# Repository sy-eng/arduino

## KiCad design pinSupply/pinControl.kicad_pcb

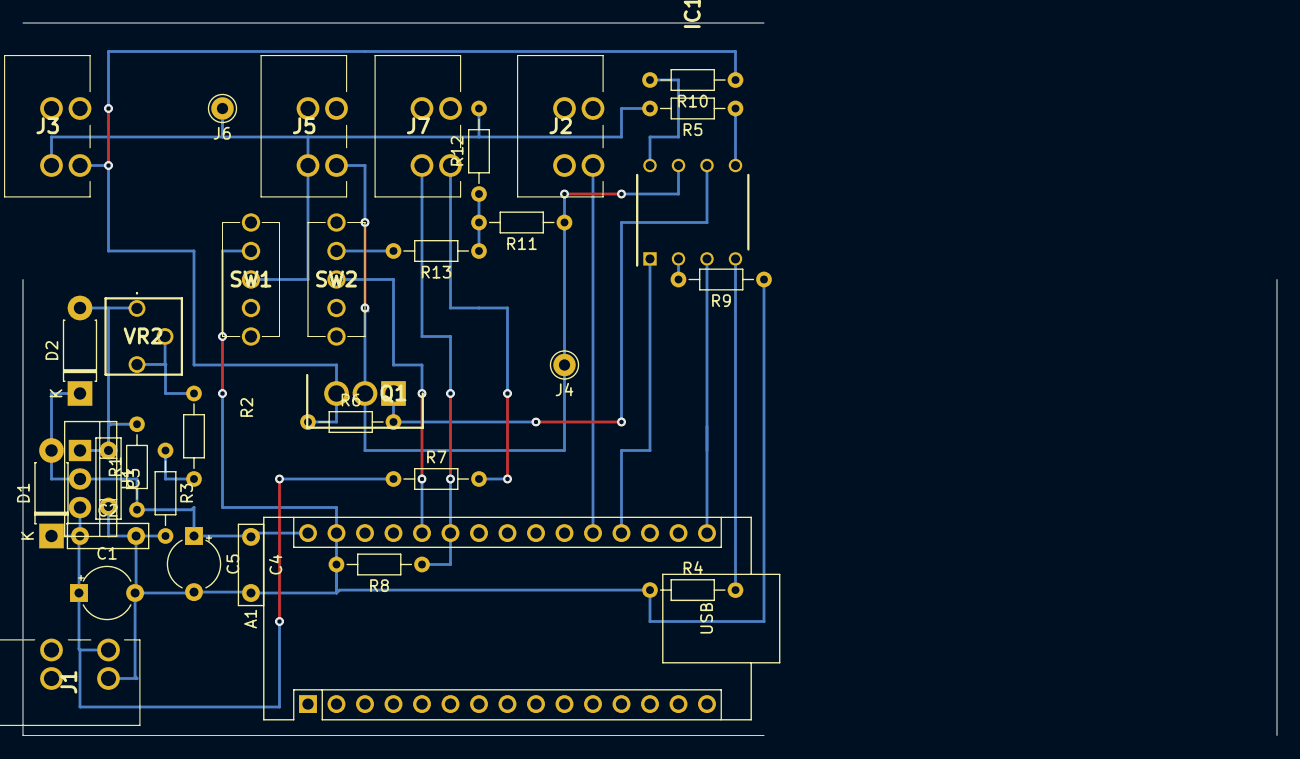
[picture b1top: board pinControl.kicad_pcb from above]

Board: 2 copper layers, 111.8 x 63.5 mm, 34 parts (0 on the bottom side), 22 nets.

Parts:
A1: Arduino_Nano_v3.x; Arduino_Nano
C1, C5: 47u; CP_Radial_Tantal_D4.5mm_P5.00mm
C2, C3: 0.1u; C_Rect_L7.0mm_W2.0mm_P5.00mm
C4: 1u; C_Rect_L7.0mm_W2.0mm_P5.00mm
D1, D2: D; D_DO-41_SOD81_P7.62mm_Horizontal
IC1: TLP521-2; DIP832W60P254L966H380Q8N
J1, J2, J3, J5, J7: TB401-1-2-E; TB40112E
J4, J6: Conn_01x01_Male; Pin_D1.0mm_L10.0mm
Q1: 2SJ334; TO254P470X1000X2090-3P
R1: 220; R_Axial_DIN0204_L3.6mm_D1.6mm_P7.62mm_Horizontal
R2: 100; R_Axial_DIN0204_L3.6mm_D1.6mm_P7.62mm_Horizontal
R3, R13: 1k; R_Axial_DIN0204_L3.6mm_D1.6mm_P7.62mm_Horizontal
R4, R8, R9: 470; R_Axial_DIN0204_L3.6mm_D1.6mm_P7.62mm_Horizontal
R5, R6: 4.7k; R_Axial_DIN0204_L3.6mm_D1.6mm_P7.62mm_Horizontal
R7, R10, R12: 2.2k; R_Axial_DIN0204_L3.6mm_D1.6mm_P7.62mm_Horizontal
R11: 10k; R_Axial_DIN0204_L3.6mm_D1.6mm_P7.62mm_Horizontal
SW1, SW2: 2MS1T1B4VS2QES
U1: LM317_TO-220; TO-220-3_Vertical
VR2: GF063P 200; GF063P

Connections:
+8V: A1.30 (VIN), C4.1, C5.1, D1.2 (A), D2.1 (K), R1.1, U1.2 (VO)
+24V: C1.1, C2.1, D1.1 (K), J1.3, R7.1, U1.3 (VI)
GND: A1.29 (GND), C1.2, C2.2, C3.2, C4.2, C5.2, J1.4, R3.2, R4.1, R8.2, R9.1, SW1.1 (NO)
GNDPWR: J3.4, J5.4, J6.1, R5.2, R12.2, SW1.2 (COM)
unnamed: A1.16 (D13), IC1.3 (ANODE_2)
unnamed: A1.19 (A0), IC1.1 (ANODE_1)
unnamed: A1.20 (A1), J2.3
unnamed: C3.1, D2.2 (A), R1.2, U1.1 (ADJ), VR2.1 (CCW)
unnamed: IC1.2 (CATHODE_1), R9.2
unnamed: IC1.4 (CATHODE_2), R4.2
unnamed: IC1.5 (EMITTER_1), R5.1
unnamed: IC1.6 (COLLECTOR_1), Q1.1, R6.2
unnamed: IC1.7 (EMITTER_2), J4.1, J5.3, Q1.2, R11.1
unnamed: IC1.8 (COLLECTOR_2), R10.2
unnamed: J7.3, R7.2
unnamed: R2.1, VR2.2 (WIPER), VR2.3 (CW)
unnamed: R2.2, R3.1
unnamed: R11.2, R12.1, R13.1
unnamed: R13.2, SW2.1 (NO)
OUT_REF: A1.26 (A7), SW2.2 (COM)
PROX_OUT: A1.25 (A6), J7.4, R8.1
VPP: J3.3, Q1.3, R6.1, R10.1

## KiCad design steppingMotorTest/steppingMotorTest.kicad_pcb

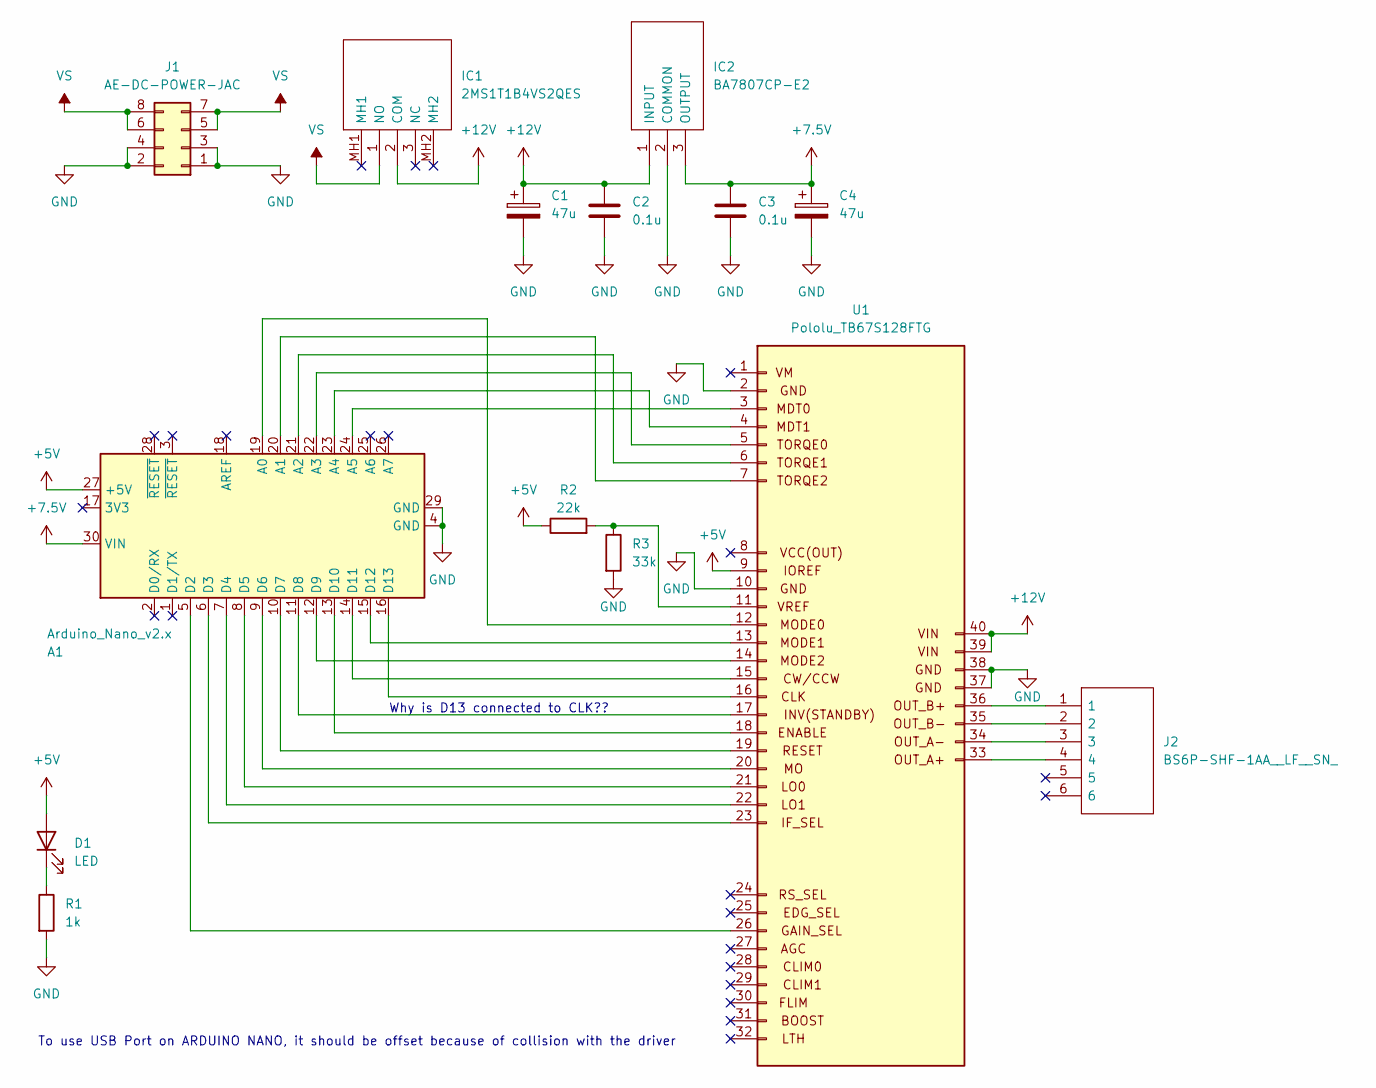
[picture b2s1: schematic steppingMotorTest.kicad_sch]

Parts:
A1: Arduino_Nano_v2.x; Arduino_Nano
C1, C4: 47u; CP_Radial_D5.0mm_P2.50mm
C2, C3: 0.1u; C_Disc_D4.3mm_W1.9mm_P5.00mm
D1: LED; LED_D5.0mm
IC1: 2MS1T1B4VS2QES; Manufacturer_Part_Number 2MS1T1B4VS2QES; Mouser Part Number N/A
IC2: BA7807CP-E2; TO254P460X1010X1700-3P; Manufacturer_Part_Number BA7807CP-E2; Mouser Part Number 755-BA7807CP-E2
J1: AE-DC-POWER-JAC; AE-DC-POWER-JACK-DIP
J2: BS6P-SHF-1AA__LF__SN_; HDRRA6W64P0X250_1X6_1500X600X560P; Manufacturer_Part_Number BS6P-SHF-1AA (LF)(SN)
R1: 1k; R_Axial_DIN0204_L3.6mm_D1.6mm_P7.62mm_Horizontal
R2: 22k; R_Axial_DIN0204_L3.6mm_D1.6mm_P7.62mm_Horizontal
R3: 33k; R_Axial_DIN0204_L3.6mm_D1.6mm_P7.62mm_Horizontal
U1: Pololu_TB67S128FTG

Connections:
+5V: A1.27 (+5V), D1.2 (A), R2.1, U1.9
+7.5V: A1.30 (VIN), C3.1, C4.1, IC2.3 (OUTPUT)
+12V: C1.1, C2.1, IC1.2 (COM), IC2.1 (INPUT), U1.39, U1.40
GND: A1.4 (GND), A1.29 (GND), C1.2, C2.2, C3.2, C4.2, IC2.2 (COMMON), J1.1, J1.2, J1.3, J1.4, R1.2, R3.2, U1.2, U1.10, U1.37, U1.38
unnamed: A1.5 (D2), U1.26
unnamed: A1.6 (D3), U1.23
unnamed: A1.7 (D4), U1.22
unnamed: A1.8 (D5), U1.21
unnamed: A1.9 (D6), U1.20
unnamed: A1.10 (D7), U1.19
unnamed: A1.11 (D8), U1.17
unnamed: A1.12 (D9), U1.14
unnamed: A1.13 (D10), U1.18
unnamed: A1.14 (D11), U1.15
unnamed: A1.15 (D12), U1.13
unnamed: A1.16 (D13), U1.16
unnamed: A1.19 (A0), U1.12
unnamed: A1.20 (A1), U1.7
unnamed: A1.21 (A2), U1.6
unnamed: A1.22 (A3), U1.5
unnamed: A1.23 (A4), U1.4
unnamed: A1.24 (A5), U1.3
unnamed: D1.1 (K), R1.1
unnamed: J2.1, U1.36
unnamed: J2.2, U1.35
unnamed: J2.3, U1.34
unnamed: J2.4, U1.33
unnamed: R2.2, R3.1, U1.11
VS: IC1.1 (NO), J1.5, J1.6, J1.7, J1.8

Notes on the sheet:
To use USB Port on ARDUINO NANO, it should be offset because of collision with the driver
Why is D13 connected to CLK??

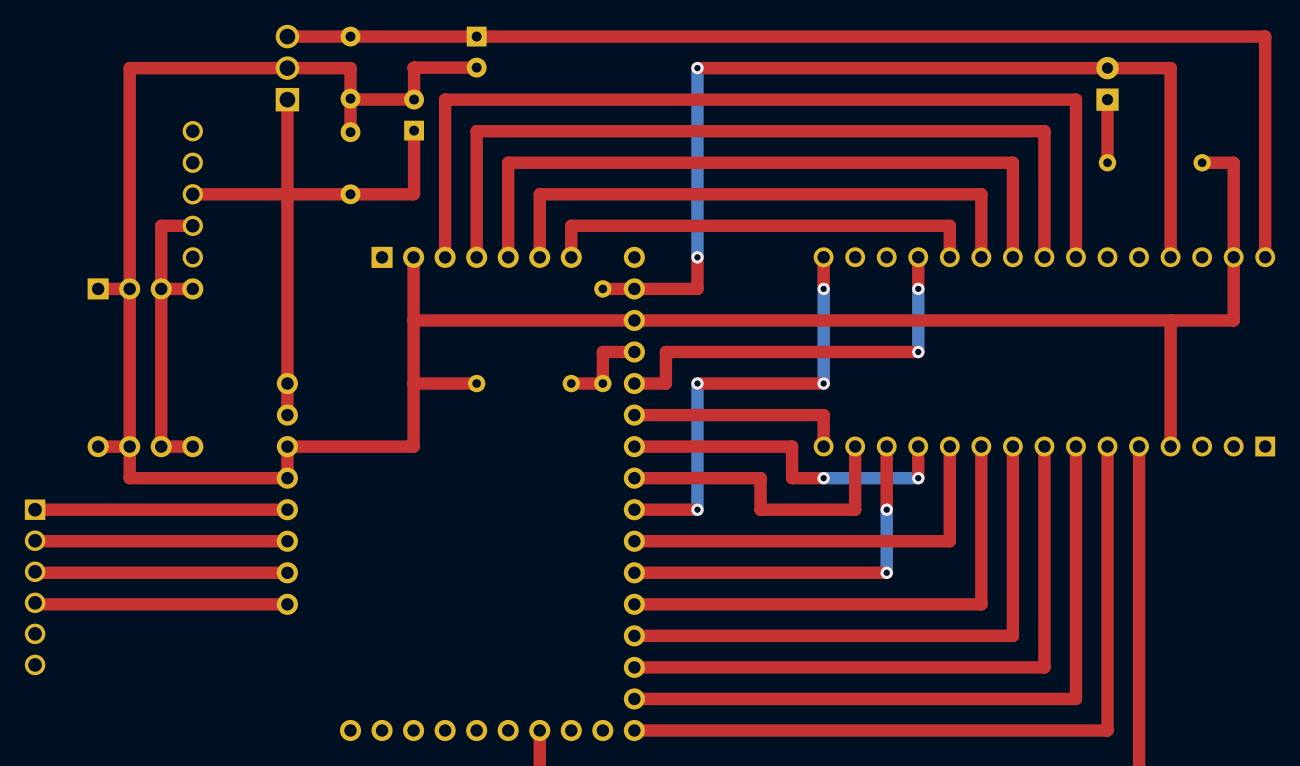
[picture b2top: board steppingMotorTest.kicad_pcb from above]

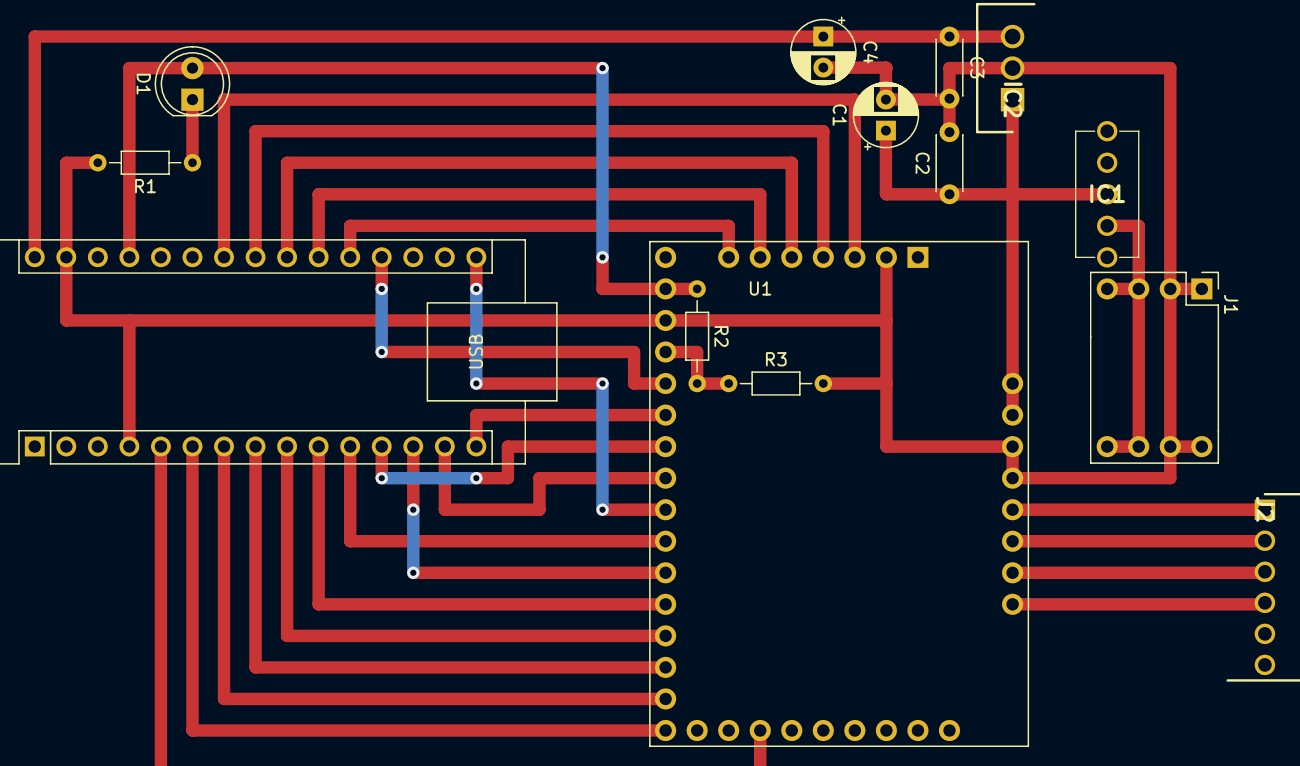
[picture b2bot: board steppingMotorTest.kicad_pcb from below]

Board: 2 copper layers, 14 parts (14 on the bottom side), 29 nets.

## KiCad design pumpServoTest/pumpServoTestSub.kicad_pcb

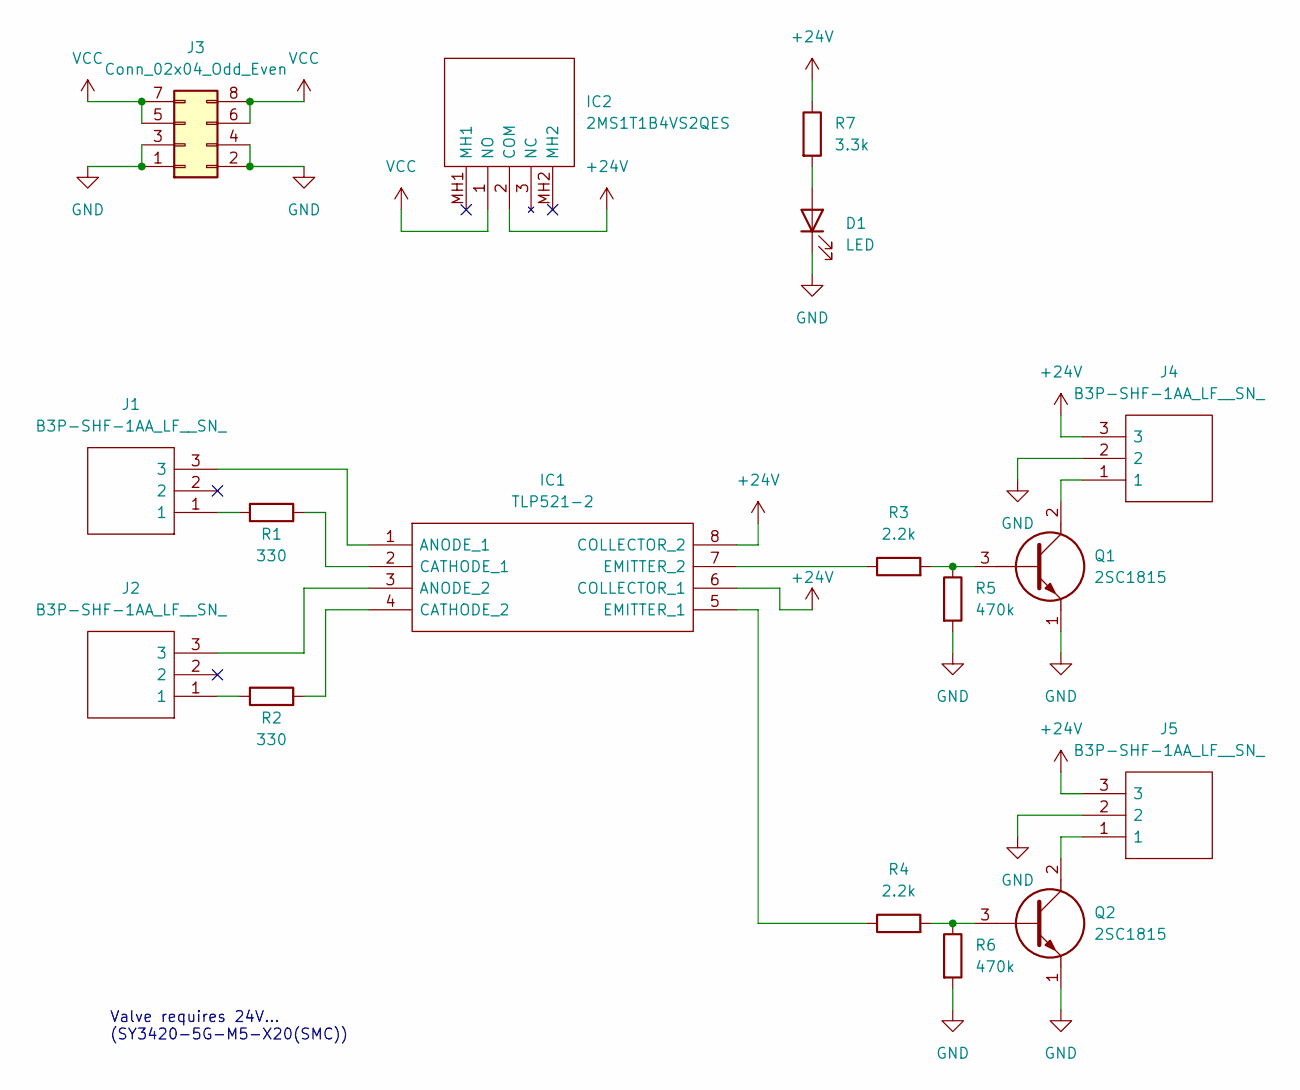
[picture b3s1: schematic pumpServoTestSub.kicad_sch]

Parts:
D1: LED; LED_D5.0mm
IC1: TLP521-2; DIP832W60P254L966H380Q8N; Manufacturer_Part_Number TLP521-2
IC2: 2MS1T1B4VS2QES; Manufacturer_Part_Number 2MS1T1B4VS2QES; Mouser Part Number N/A
J1, J2, J4, J5: B3P-SHF-1AA_LF__SN_; HDRV3W80P0X250_1X3_750X560X920P; Manufacturer_Part_Number B3P-SHF-1AA(LF)(SN)
J3: Conn_02x04_Odd_Even; AE-DC-POWER-JACK-DIP
Q1, Q2: 2SC1815; CS_TO-92; Manufacturer_Part_Number 2SC1815; Mouser Part Number 610-2SC1815
R1, R2: 330; R_Axial_DIN0204_L3.6mm_D1.6mm_P7.62mm_Horizontal
R3, R4: 2.2k; R_Axial_DIN0204_L3.6mm_D1.6mm_P7.62mm_Horizontal
R5, R6: 470k; R_Axial_DIN0204_L3.6mm_D1.6mm_P7.62mm_Horizontal
R7: 3.3k; R_Axial_DIN0204_L3.6mm_D1.6mm_P7.62mm_Horizontal

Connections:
+24V: IC1.6 (COLLECTOR_1), IC1.8 (COLLECTOR_2), IC2.2 (COM), J4.3, J5.3, R7.1
GND: D1.1 (K), J3.1, J3.2, J3.3, J3.4, J4.2, J5.2, Q1.1, Q2.1, R5.2, R6.2
unnamed: D1.2 (A), R7.2
unnamed: IC1.1 (ANODE_1), J1.3
unnamed: IC1.2 (CATHODE_1), R1.2
unnamed: IC1.3 (ANODE_2), J2.3
unnamed: IC1.4 (CATHODE_2), R2.2
unnamed: IC1.5 (EMITTER_1), R4.1
unnamed: IC1.7 (EMITTER_2), R3.1
unnamed: J1.1, R1.1
unnamed: J2.1, R2.1
unnamed: J4.1, Q1.2
unnamed: J5.1, Q2.2
unnamed: Q1.3, R3.2, R5.1
unnamed: Q2.3, R4.2, R6.1
VCC: IC2.1 (NO), J3.5, J3.6, J3.7, J3.8

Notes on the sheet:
Valve requires 24V... (SY3420-5G-M5-X20(SMC))

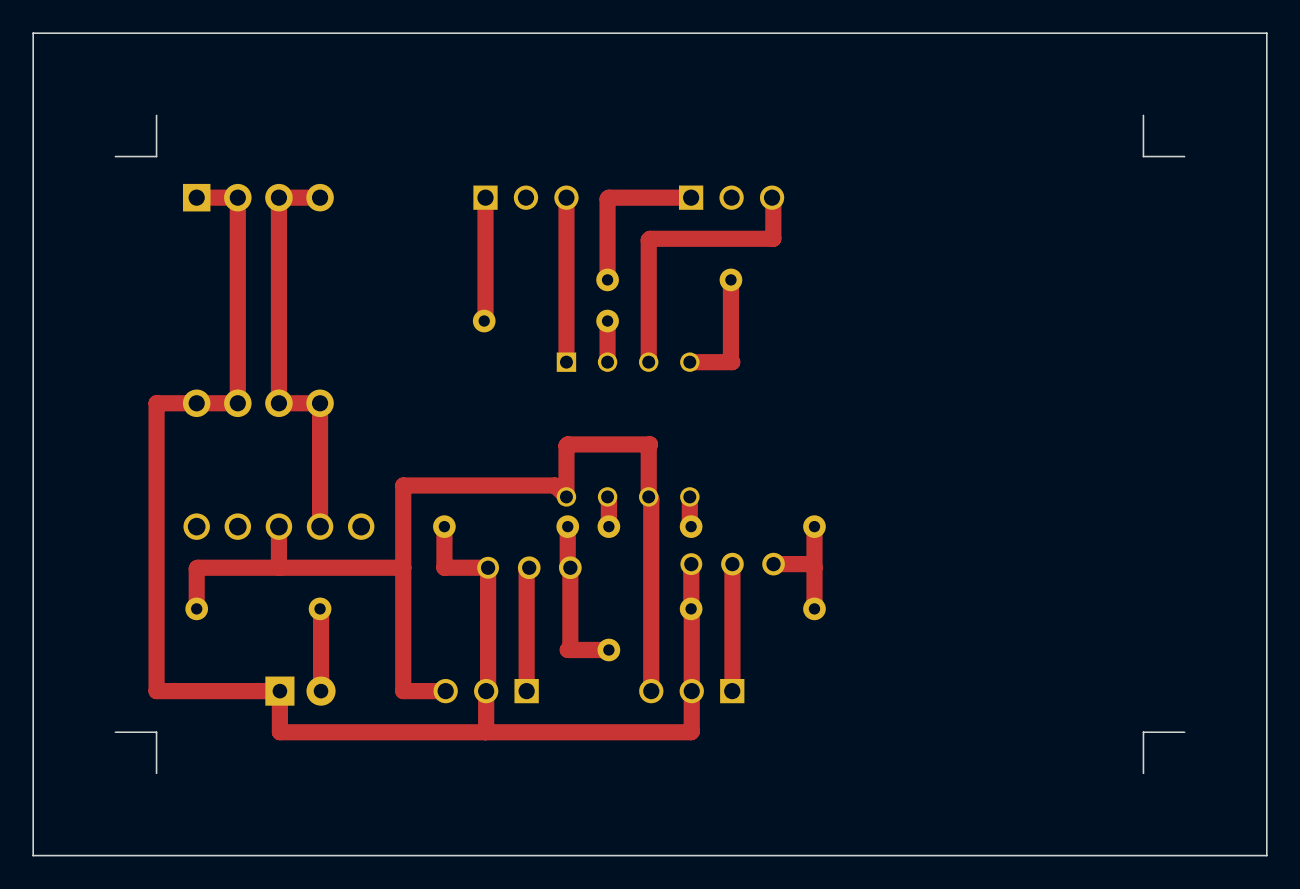
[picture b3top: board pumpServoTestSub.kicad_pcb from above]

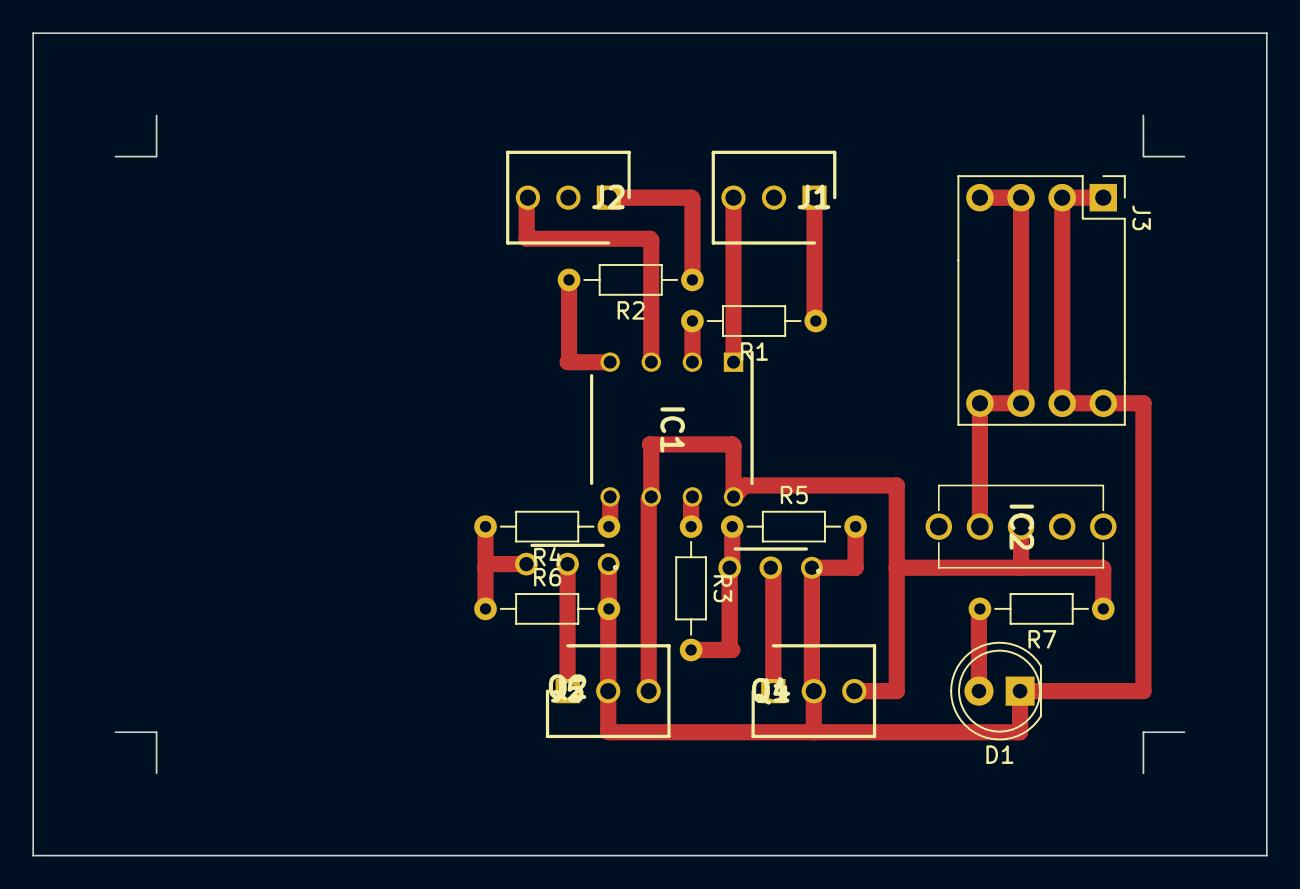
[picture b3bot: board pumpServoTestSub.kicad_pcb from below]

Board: 2 copper layers, 76.2 x 50.8 mm, 17 parts (17 on the bottom side), 16 nets.

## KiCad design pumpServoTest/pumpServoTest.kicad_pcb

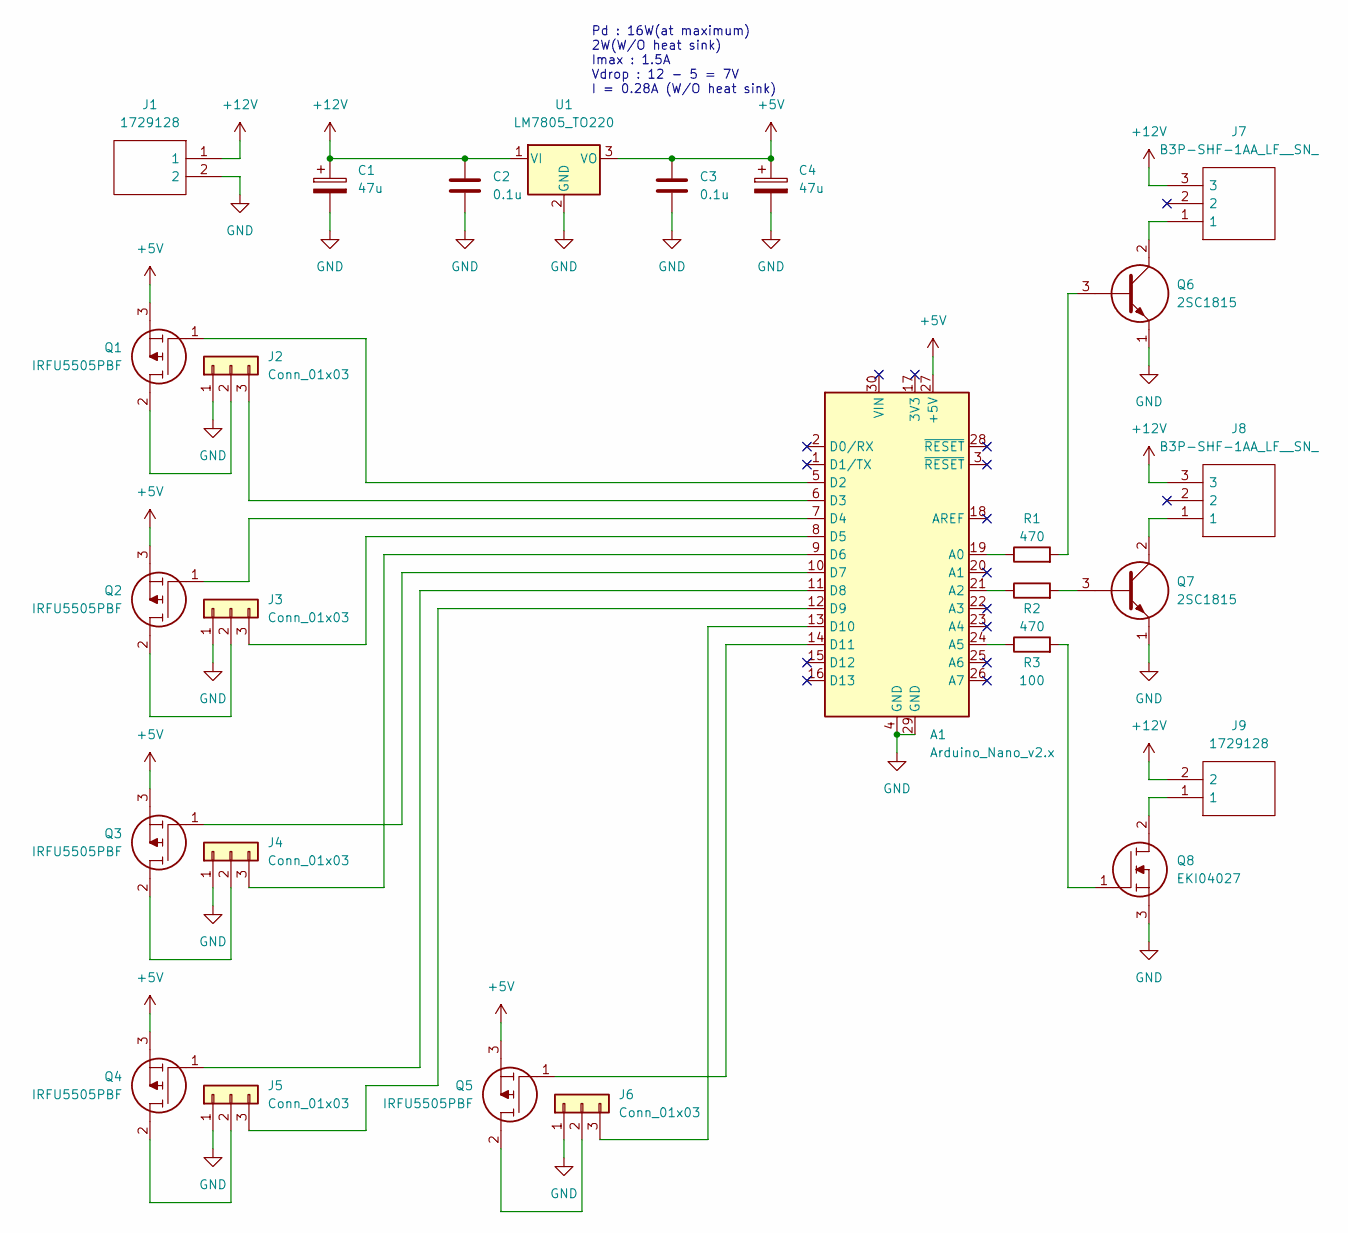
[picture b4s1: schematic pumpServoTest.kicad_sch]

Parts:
A1: Arduino_Nano_v2.x; Arduino_Nano
C1, C4: 47u; CP_Radial_D8.0mm_P5.00mm
C2, C3: 0.1u; C_Rect_L7.0mm_W2.0mm_P5.00mm
J1, J9: 1729128; Manufacturer_Part_Number 1729128; Mouser Part Number 651-1729128
J2, J3, J4, J5, J6: Conn_01x03; PinHeader_1x03_P2.54mm_Vertical
J7, J8: B3P-SHF-1AA_LF__SN_; HDRV3W80P0X250_1X3_750X560X920P; Manufacturer_Part_Number B3P-SHF-1AA(LF)(SN)
Q1, Q2, Q3, Q4, Q5: IRFU5505PBF; TO229P239X654X978-3P_tmp; Manufacturer_Part_Number IRFU5505PBF; Mouser Part Number 942-IRFU5505PBF
Q6, Q7: 2SC1815; CS_TO-92; Manufacturer_Part_Number 2SC1815; Mouser Part Number 610-2SC1815
Q8: EKI04027; TO254P470X990X1965-3P; Manufacturer_Part_Number EKI04027
R1: 470; R_Axial_DIN0204_L3.6mm_D1.6mm_P7.62mm_Horizontal
R2: 470; R_0603_1608Metric
R3: 100; R_Axial_DIN0204_L3.6mm_D1.6mm_P7.62mm_Horizontal
U1: LM7805_TO220; TO-220-3_Vertical

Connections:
+5V: A1.27 (+5V), C3.1, C4.1, Q1.3, Q2.3, Q3.3, Q4.3, Q5.3, U1.3 (VO)
+12V: C1.1, C2.1, J1.1, J7.3, J8.3, J9.2, U1.1 (VI)
GND: A1.4 (GND), A1.29 (GND), C1.2, C2.2, C3.2, C4.2, J1.2, J2.1, J3.1, J4.1, J5.1, J6.1, Q6.1, Q7.1, Q8.3, U1.2 (GND)
unnamed: A1.5 (D2), Q1.1
unnamed: A1.6 (D3), J2.3
unnamed: A1.7 (D4), Q2.1
unnamed: A1.8 (D5), J3.3
unnamed: A1.9 (D6), J4.3
unnamed: A1.10 (D7), Q3.1
unnamed: A1.11 (D8), Q4.1
unnamed: A1.12 (D9), J5.3
unnamed: A1.13 (D10), J6.3
unnamed: A1.14 (D11), Q5.1
unnamed: A1.19 (A0), R1.1
unnamed: A1.21 (A2), R2.1
unnamed: A1.24 (A5), R3.1
unnamed: J2.2, Q1.2
unnamed: J3.2, Q2.2
unnamed: J4.2, Q3.2
unnamed: J5.2, Q4.2
unnamed: J6.2, Q5.2
unnamed: J7.1, Q6.2
unnamed: J8.1, Q7.2
unnamed: J9.1, Q8.2
unnamed: Q6.3, R1.2
unnamed: Q7.3, R2.2
unnamed: Q8.1, R3.2

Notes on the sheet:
Pd : 16W(at maximum) 2W(W/O heat sink) Imax : 1.5A Vdrop : 12 - 5 = 7V I = 0.28A (W/O heat sink)

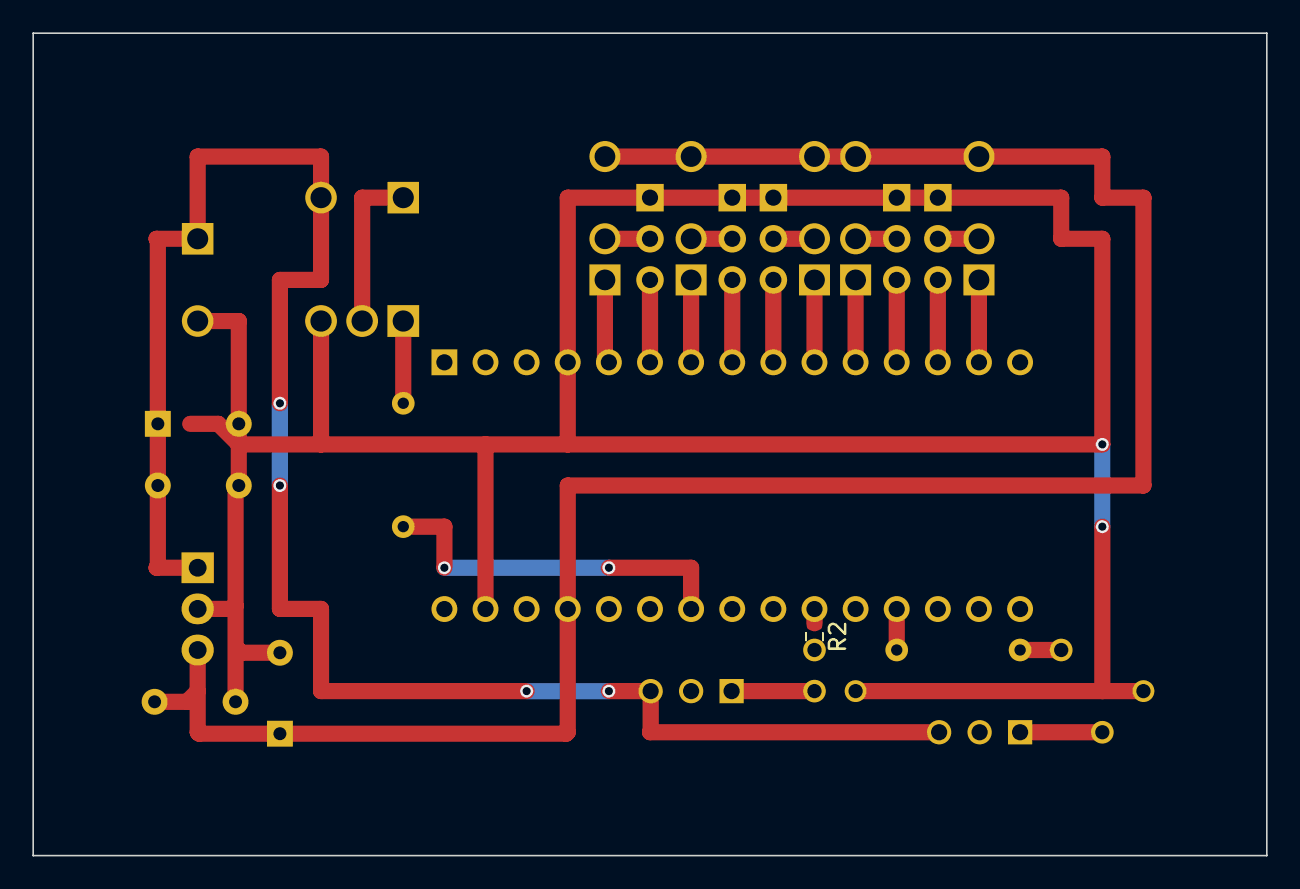
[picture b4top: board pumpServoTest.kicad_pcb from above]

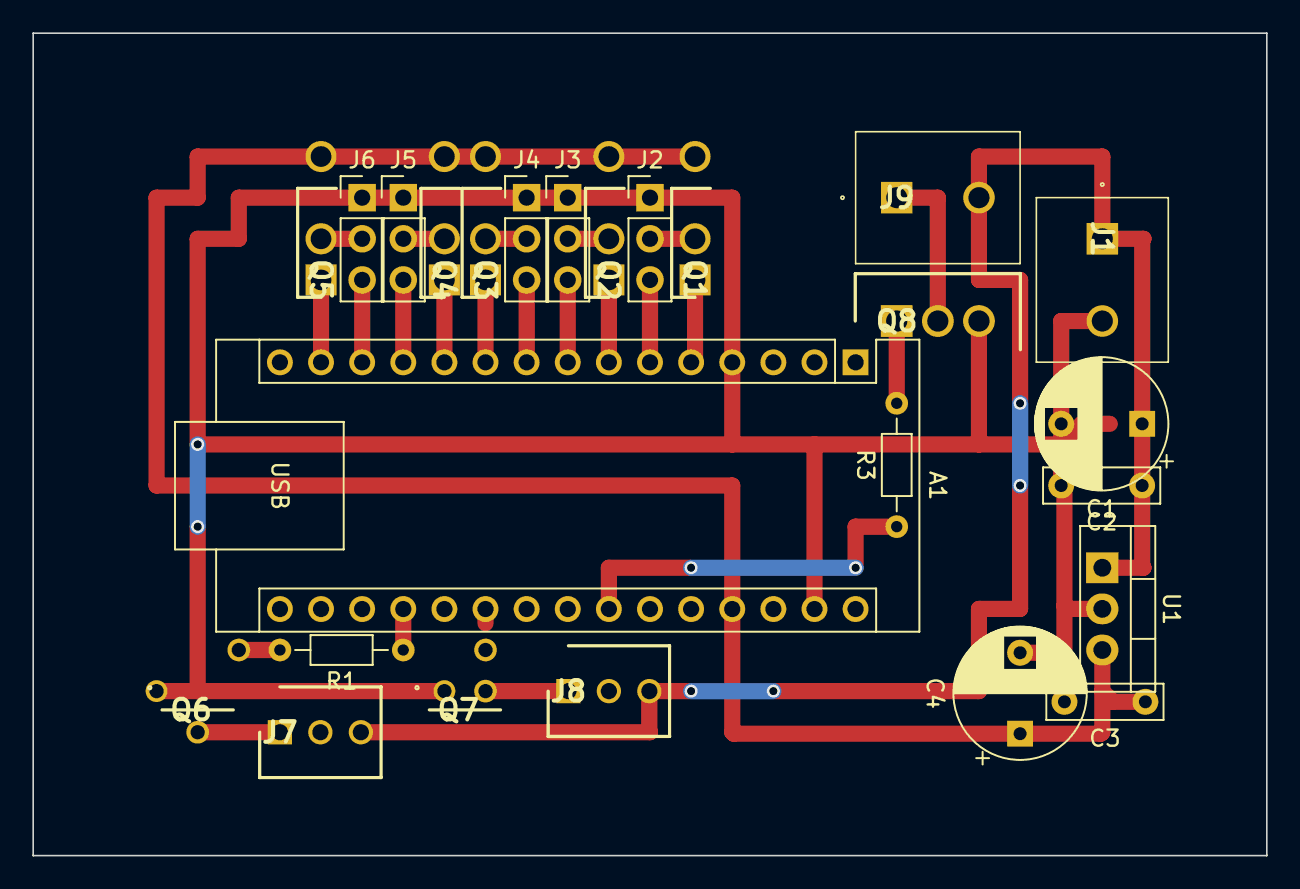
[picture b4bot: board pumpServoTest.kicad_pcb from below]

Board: 2 copper layers, 76.2 x 50.8 mm, 26 parts (25 on the bottom side), 27 nets.

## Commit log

2022-12-19 Rename pumpServoTest.ino to pumpServoTest/pumpServoTest.ino
2022-12-28 Rename steppingMotorTest.ino to steppingMotorTest/steppingMotorTest.ino
2023-09-03 Rename pinSupply.ino to pinSupply/pinSupply.ino
